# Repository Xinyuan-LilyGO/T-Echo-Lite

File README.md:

<!--
 * @Description: None
 * @Author: LILYGO_L
 * @Date: 2023-09-11 16:13:14
 * @LastEditTime: 2026-07-14 09:57:59
 * @License: GPL 3.0
-->
<h1 align = "center">T-Echo-Lite</h1>

## **English | [中文](./README_CN.md)**

## Version iteration:
| Version                              | Update date                       |
| :-------------------------------: | :-------------------------------: |
| T-Echo-Lite_V1.0            | 2024-12-06                         |
| T-Echo-Lite-Kit_V1.0            | 2025-10-14                         |

## PurchaseLink
| Product                     | SOC           |  FLASH  |  PSRAM   | Link                   |
| :------------------------: | :-----------: |:-------: | :---------: | :------------------: |
| T-Echo-Lite_V1.0   | nRF52840 |   1M   |256kB| [LILYGO Mall](https://lilygo.cc/products/t-echo-lite?_pos=1&_sid=79b4c08e7&_ss=r&variant=45331277906101) |
| T-Echo-Lite-Kit_V1.0   |  |  || NULL |

## Directory
- [Describe](#describe)
- [Preview](#preview)
- [Module](#module)
- [SoftwareDeployment](#SoftwareDeployment)
- [PinOverview](#pinoverview)
- [RelatedTests](#RelatedTests)
- [FAQ](#faq)
- [Project](#project)

## Describe

T-Echo-Lite is a lightweight version based on T-Echo, featuring a smaller volume and lower power consumption design compared to T-Echo. Its minimum deep sleep power consumption can reach 2μA to 10μA (due to differences in onboard components on different boards, power consumption performance may vary; the minimum power consumption mentioned here is based on the engineering board tested by the LILYGO laboratory). The board is equipped with a rich set of features, including an inertial sensor, LORA module, solar charging function (5V), external GPS, and more. Its excellent power consumption performance allows T-Echo-Lite to achieve superior battery life.

T-Echo-Lite-Kit is a baseboard expansion for T-Echo-Lite, primarily extending peripherals such as a keyboard, speaker, microphone, and vibration motor.

> [!NOTE]
> T-Echo-Lite-Kit and T-Echo-Lite-KeyShield refer to the same product. The legacy name is retained only in existing file and directory names.

> [!IMPORTANT]
> Important note: The L76K module and the ICM20948 module are external expansion modules. The default purchase link does not include these two modules (the ICM20948 module is connected via soldering, while the L76K module is connected via pin headers). They need to be purchased separately.

## Preview

### Actual Product Image

---

---

## Module

### T-Echo-Lite Section
### 1. MCU
*   Chip: nRF52840
*   RAM: 256kB
*   FLASH: 1M
*   Related Documentation:
    > [nRF52840_Datasheet](https://docs.nordicsemi.com/bundle/ps_nrf52840/page/keyfeatures_html5.html)

### 2. Screen
*   Name: GDEM0122T61
*   Size: 1.22 inches
*   Resolution: 176x192px
*   Screen Type: E-PAPER
*   Driver Chip: SSD1681
*   Bus Communication Protocol: IIC
*   Additional Notes: Fast refresh is not supported (after consulting the screen manufacturer, they replied that it is not supported), it is recommended to use full refresh only
*   Dependent Libraries:
    >[Adafruit_EPD](https://github.com/adafruit/Adafruit_EPD)  
    >[Adafruit_BusIO](https://github.com/adafruit/Adafruit_BusIO)  
    >[Adafruit_SPIFlash](https://github.com/adafruit/Adafruit_SPIFlash)  
    >[Adafruit-GFX-Library](https://github.com/adafruit/Adafruit-GFX-Library)
*   Related Documentation:
    > [GDEM0122T61](./information/GDEM0122T61.pdf)  
    > [SSD1681](./information/SSD1681.pdf)  

### 3. LORA
*   Chip Module: S62F
*   Chip: SX1262
*   Bus Communication Protocol: SPI
*   Dependent Libraries:
    >[RadioLib](https://github.com/jgromes/RadioLib)  
    >[Adafruit_BusIO](https://github.com/adafruit/Adafruit_BusIO)  
    >[Adafruit_SPIFlash](https://github.com/adafruit/Adafruit_SPIFlash)
*   Related Documentation:
    > [S62F](./information/S62F.pdf)  
    > [S62F Application Note](./information/S62F_ApplicationNote_Ver_D.pdf)

#### S62F Hardware Configuration

* RF switch: T-Echo-Lite uses AcSiP control mode A. The nRF52840 drives `RF_VC1` (`P0.27`) and `RF_VC2` (`P1.01`) directly. `DIO2` (`P0.05`) is routed separately and is not hardwired to the RF switch on this board. Set `RF_VC1/RF_VC2` to `HIGH/LOW` for transmit and `LOW/HIGH` for receive.
* TCXO: The embedded 32 MHz TCXO is controlled internally by SX1262 `DIO3`. Set `tcxoVoltage` explicitly to `3.0 V` when initializing the radio.
* Regulator: `VREG` and `DCC_SW` are connected through a 15 uH inductor. Use the DC-DC regulator mode (`useRegulatorLDO = false`).

### 4. GPS
*   Chip Module: L76K
*   Bus Communication Protocol: UART
*   Dependent Libraries:
    >[TinyGPSPlus](https://github.com/mikalhart/TinyGPSPlus)
*   Related Documentation:
    > [L76KB-A58](./information/L76KB-A58.pdf)  

> [!IMPORTANT]
> Important note: The L76K module is an external expansion module. The default purchase link does not include this module, so it needs to be purchased separately.

### 5. Inertial Measurement Unit
*   Chip: ICM20948
*   Bus Communication Protocol: IIC
*   Dependent Libraries:
    >[ICM20948_WE](https://github.com/wollewald/ICM20948_WE)
*   Related Documentation:
    > [ICM20948](./information/ICM20948.pdf)  

> [!IMPORTANT]
> Important note: The ICM20948 module is an external expansion module. The default purchase link does not include this module, so it needs to be purchased separately.

### 6. Flash
*   Chip: ZD25WQ32C or ZD25Q32D
*   Bus Communication Protocol: SPI
*   Dependent Libraries:
    >[Adafruit_BusIO](https://github.com/adafruit/Adafruit_BusIO)  
    >[Adafruit_SPIFlash](https://github.com/adafruit/Adafruit_SPIFlash)  
*   Related Documentation:
    > [ZD25WQ32CEIGR](./information/ZD25WQ32CEIGR.pdf)
    >[ZD25Q32DTIGT](./information/ZD25Q32DTIGT.pdf)

### T-Echo-Lite-Kit Section
### 1. Keyboard Backlight

* Driver Chip: AW21009QNR
* Bus Communication Protocol: IIC
* Dependent Libraries:
    >[cpp_bus_driver](https://github.com/Llgok/cpp_bus_driver)
* Related Information:
    >[AW21009QNR](./information/AW21009QNR.pdf)

### 2. Vibration

* Driver Chip: AW86224
* Bus Communication Protocol: IIC
* Dependent Libraries:
    >[cpp_bus_driver](https://github.com/Llgok/cpp_bus_driver)
* Related Information:
    >[AW86224AFCR](./information/AW86224AFCR.pdf)

### 3. Speaker Microphone

* Driver Chip: ES8311
* Bus Communication Protocols: IIC, IIS
* Dependent Libraries:
    >[cpp_bus_driver](https://github.com/Llgok/cpp_bus_driver)
* Related Information:
    >[ES8311](./information/ES8311.pdf)

### 4. Keyboard

* Driver Chip: TCA8418
* Bus Communication Protocol: IIC
* Dependent Libraries:
    >[cpp_bus_driver](https://github.com/Llgok/cpp_bus_driver)
* Related Information:
    >[tca8418](./information/tca8418.pdf)

## SoftwareDeployment

### Examples Support

### T-Echo-Lite Examples
| Example | `[Arduino IDE (Adafruit_nRF52_V1.6.1)]` <br /> `[PlatformIO (nordicnrf52_V10.6.0)]` <br /> Support | Description | Picture |
| ------  | ------  | ------ | ------ | 
| [Battery_Measurement](./examples/T-Echo-Lite/Battery_Measurement) | <p align="center">![alt text][supported]  |  |  |
| [BLE_Uart](./examples/T-Echo-Lite/BLE_Uart) | <p align="center">![alt text][supported]  |  |  |
| [Button_Triggered](./examples/T-Echo-Lite/Button_Triggered) | <p align="center">![alt text][supported]  |  |  |
| [Display](./examples/T-Echo-Lite/Display) | <p align="center">![alt text][supported]  |  |  |
| [Display_BLE_Uart](./examples/T-Echo-Lite/Display_BLE_Uart) | <p align="center">![alt text][supported]  |  |  |
| [Display_SX1262](./examples/T-Echo-Lite/Display_SX1262) | <p align="center">![alt text][supported]  |  |  |
| [Flash](./examples/T-Echo-Lite/Flash) | <p align="center">![alt text][supported]  |  |  |
| [Flash_Erase](./examples/T-Echo-Lite/Flash_Erase) | <p align="center">![alt text][supported]  |  |  |
| [Flash_Speed_Test](./examples/T-Echo-Lite/Flash_Speed_Test) | <p align="center">![alt text][supported]  |  |  |
| [GPS](./examples/T-Echo-Lite/GPS) | <p align="center">![alt text][supported]  |  |  |
| [GPS_Full](./examples/T-Echo-Lite/GPS_Full) | <p align="center">![alt text][supported]  |  |  |
| [ICM20948](./examples/T-Echo-Lite/ICM20948) | <p align="center">![alt text][supported]  |  |  |
| [IIC_Scan_2](./examples/T-Echo-Lite/IIC_Scan_2) | <p align="center">![alt text][supported]  |  |  |
| [nrf52840_module](./examples/T-Echo-Lite/nrf52840_module) | <p align="center">![alt text][supported]  |  |  |
| [Original_Test](./examples/T-Echo-Lite/Original_Test) |<p align="center">![alt text][supported]  | Product factory original testing |  |
| [Sleep_Wake_Up](./examples/T-Echo-Lite/Sleep_Wake_Up) | <p align="center">![alt text][supported]  |  |  |
| [SX126x_PingPong](./examples/T-Echo-Lite/SX126x_PingPong) | <p align="center">![alt text][supported]  |  |  |
| [SX126x_PingPong_2](./examples/T-Echo-Lite/SX126x_PingPong_2) | <p align="center">![alt text][supported]  |  |  |
| [sx126x_tx_continuous_wave](./examples/T-Echo-Lite/sx126x_tx_continuous_wave) | <p align="center">![alt text][supported]  |  |  |

### T-Echo-Lite-Kit Examples
| Example | `[Arduino IDE (Adafruit_nRF52_V1.6.1)]` <br /> `[PlatformIO (nordicnrf52_V10.6.0)]` <br /> Support | Description | Picture |
| ------  | ------  | ------ | ------ | 
| [aw21009qnr](./examples/T-Echo-Lite-KeyShield/aw21009qnr) | <p align="center">![alt text][supported]  |  |  |
| [aw86224](./examples/T-Echo-Lite-KeyShield/aw86224) | <p align="center">![alt text][supported]  |  |  |
| [es8311](./examples/T-Echo-Lite-KeyShield/es8311) | <p align="center">![alt text][supported]  |  |  |
| [general_test](./examples/T-Echo-Lite-KeyShield/general_test) | <p align="center">![alt text][supported]  | Product factory original testing  |  |
| [tca8418](./examples/T-Echo-Lite-KeyShield/tca8418) | <p align="center">![alt text][supported]  |  |  |
| [voice_speaker](./examples/T-Echo-Lite-KeyShield/voice_speaker) | <p align="center">![alt text][supported]  |  |  |

[supported]: https://img.shields.io/badge/-supported-green "example"

| Bootloader | Description | Picture |
| ------  | ------  | ------ |
| [bootloader](./bootloader/) | |  |

| Firmware | Description | Picture |
| ------  | ------  | ------ |
| [T-Echo-Lite_Original_Test](./firmware/[T-Echo-Lite_V1.0][Original_Test]_firmware/)| Product factory original testing |  |
| [T-Echo-Lite-Kit_general_test](./firmware/[T-Echo-Lite-KeyShield_V1.0][general_test]_firmware/)| Product factory original testing |  |

### IDE and Flashing

#### PlatformIO
1. Install [VisualStudioCode](https://code.visualstudio.com/Download),choose installation based on your system type.

2. Open the "Extension" section of the Visual Studio Code software sidebar (Alternatively, use "<kbd>Ctrl</kbd>+<kbd>Shift</kbd>+<kbd>X</kbd>" to open the extension). Search for the "PlatformIO IDE" extension and download it.

3. During the installation of the extension, you can go to GitHub to download the program. You can download the main branch by clicking on the "<> Code" with green text, or you can download the program versions from the "Releases" section in the sidebar.

4. After the installation of the extension is completed, open the Explorer in the sidebar (Alternatively, use "<kbd>Ctrl</kbd>+<kbd>Shift</kbd>+<kbd>E</kbd>" go open it). Click on "Open Folder", locate the project code you just downloaded (the entire folder), and click "Add." At this point, the project files will be added to your workspace.

5. Open the "platformio.ini" file in the project folder (PlatformIO will automatically open the "platformio.ini" file corresponding to the added folder). Under the "[platformio]" section, uncomment and select the example program you want to burn (it should start with "default_envs = xxx") Then click "<kbd>[√](image/4.png)</kbd>" in the bottom left corner to compile. If the compilation is correct, connect the microcontroller to the computer and click "<kbd>[→](image/5.png)</kbd>" in the bottom left corner to download the program.

6. At this point, an error may occur, and you need to install [Python](https://www.python.org/downloads/). Open the folder "tool" -> "win10 vscode platformio start" sequentially, and execute the cmd command `python t-echo-lite_v1.0.0_setup.py` under the "win10 vscode platformio start" folder. This will complete the development board installation, and the compilation and flashing will no longer report errors.

#### Arduino

1. Install [Arduino](https://www.arduino.cc/en/software), and select the installation based on your system type.

2. Open the "example" directory of the project folder, select the example project folder, and open the file ending with ".ino" to open the Arduino IDE project workspace.

3. Open the "Tools" menu bar at the top right -> Select "Board" -> "Board Manager", find or search for "Adafruit_nRF52", and download the board file with the author named "Adafruit". Then return to the "Board" menu bar, select the board type under the "Adafruit_nRF52" board, and the selected board type is determined by the "board = xxx" header under the [env] directory in the "platformio.ini" file. If there is no corresponding board, you need to manually add the board under the "board" directory in the project folder. (If "Adafruit_nRF52" cannot be found, you need to open Preferences -> Add `https://www.adafruit.com/package_adafruit_index.json` to "Additional Board Manager URLs")
    
4. Open the menu bar "[File](image/6.png)" -> "[Preferences](image/6.png)", find the "[Project Folder Location](image/7.png)" section, and copy and paste all the library files along with the folders in the "libraries" folder under the project directory into the "libraries" folder in this directory.
    
5. Select the correct settings in the "Tools" menu, as shown in the table below.
    
| Setting                               | Value                                 |
| :-------------------------------: | :-------------------------------: |
| Board                                 | Nordic nRF52840 DK           |

6.  Select the correct port.

7.  Enable boot download mode: Press and release the RST chip reset button, wait for LED1 to light up (you must wait for LED1 to light up), then press and release the RST button again. Observe that LED1 gradually dims and then gradually lights up, indicating that the boot download mode has been entered.

8.  Click the top right "[√](image/8.png)" to compile. If there are no errors, connect the microcontroller to the computer and click the top right "[→](image/9.png)" to start the flashing process.

#### JLINK Flashing Firmware and Bootloader

1.  Install the software [nRF-Connect-for-Desktop](https://www.nordicsemi.com/Products/Development-tools/nRF-Connect-for-Desktop/Download#infotabs)

2.  Install the software [JLINK](https://www.segger.com/downloads/jlink/)

3.  Connect the JLINK pins correctly as shown in the figure below

4.  Open the software nRF-Connect-for-Desktop and install the tool [Programmer](./image/10.png) and open it

5.  Add files, select both the bootloader file and the firmware file at the same time, click [Erase&write](./image/11.png), and the flashing will be completed.

## PinOverview

For pin definitions, please refer to the configuration file: 
<br />

[t_echo_lite_config.h](./libraries/private_library/t_echo_lite_config.h)  
[t_echo_lite_keyshield_config.h](./libraries/private_library/t_echo_lite_keyshield_config.h)

## RelatedTests

### Power Dissipation
| Firmware | Program| Description | Picture |
| ------  | ------  | ------ | ------ | 
| [Sleep_Wake_Up](./firmware/[T-Echo-Lite_V1.0][Sleep_Wake_Up]_firmware/[T-Echo-Lite_V1.0][Sleep_Wake_Up]_firmware_202412040900.hex) <br /> [Sleep_Wake_Up(uf2)](./firmware/[T-Echo-Lite_V1.0][Sleep_Wake_Up]_firmware/[T-Echo-Lite_V1.0][Sleep_Wake_Up]_firmware_202412040900.uf2) | `Sleep_Wake_Up` | Minimum power consumption: 2.54uA <br /> More information can be found in the [Power Consumption Test Log](./relevant_test/PowerConsumptionTestLog_[T-Echo-Lite_V1.0]_20241210.pdf) |  |

## FAQ

* Q. After reading the above tutorials, I still don't know how to build a programming environment. What should I do?
* A. If you still don't understand how to build an environment after reading the above tutorials, you can refer to the [LilyGo-Document](https://github.com/Xinyuan-LilyGO/LilyGo-Document) document instructions to build it.

<br />

* Q. Why does Arduino IDE prompt me to update library files when I open it? Should I update them or not?
* A. Choose not to update library files. Different versions of library files may not be mutually compatible, so it is not recommended to update library files.

<br />

* Q. Why is there no debug information output from my board's USB?
* A. Please enable the "DTR" option in your serial assistant software.

<br />

* Q. Why does my board fail to flash when I use USB directly?
* A. Please press and release the RST chip reset button, wait for LED1 to light up (you must wait for LED1 to light up), then press and release the RST button again. Observe that LED1 gradually dims and then gradually lights up, indicating that the boot download mode has been entered. At this point, you can flash the board.

<br />

* Q. How should the Bluetooth antenna and Lora antenna of the T-Echo-Lite module be distinguished?
* A. The Bluetooth antenna and Lora antenna of the T-Echo-Lite module are as shown in the following figure:

<br />

## Project
* [T-Echo-Lite_V1.0](./project/T-Echo-Lite_V1.0)
* [T-Echo-Lite-Kit_V1.0](./project/T-Echo-Lite-KeyShield_V1.0)

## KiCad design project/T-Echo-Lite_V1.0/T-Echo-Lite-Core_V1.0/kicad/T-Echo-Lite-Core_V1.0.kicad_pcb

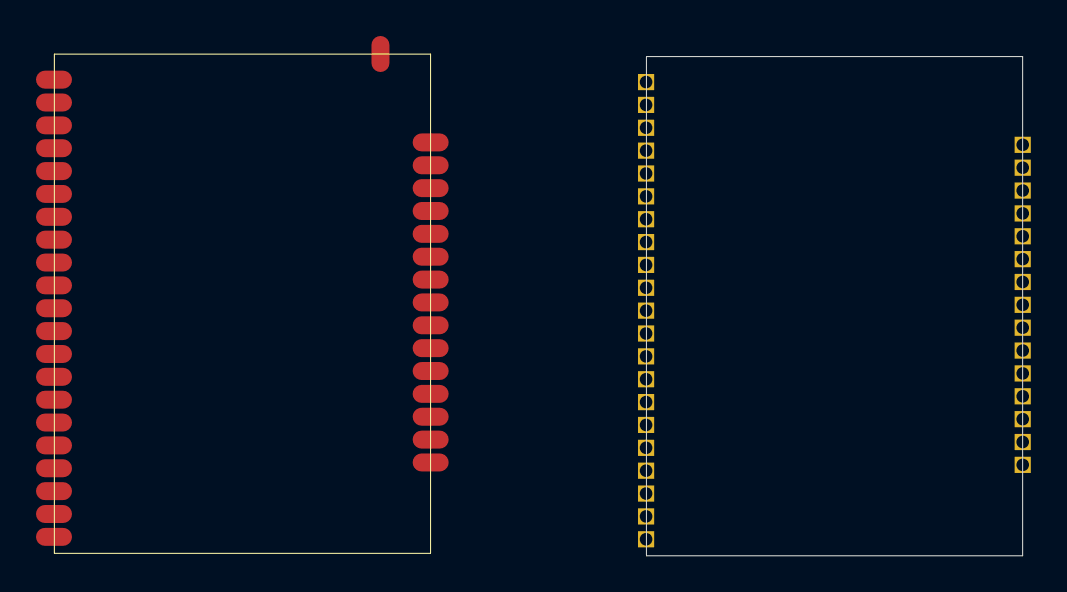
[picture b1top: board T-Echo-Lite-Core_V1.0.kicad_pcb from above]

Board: 2 copper layers, 20.9 x 27.7 mm, 3 parts (0 on the bottom side), 26 nets, no tracks yet.

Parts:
P0: SPAD___21
P3: SPAD___15
U?: T_Ech0_lite

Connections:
BUTTON: P0.9, U?.9
GND: P0.19, U?.19
P0.16: P3.13, U?.24
P0.23: P3.10, U?.27
P0.25: P3.9, U?.28
P0.29: P0.3, U?.3
P1.02: P3.8, U?.29
P1.03: P3.3, U?.34
P1.04: P3.7, U?.30
P1.05: P3.2, U?.35
P1.06: P3.6, U?.31
P1.07: P3.1, U?.36
P1.10: P0.4, U?.4
P1.11: P0.5, U?.5
P1.15: P0.2, U?.2
REST: P0.12, U?.12
SWDCLK: P0.11, U?.11
SWDIO: P0.10, U?.10
S_PWR: P0.21, U?.21
USB_D+: P0.14, U?.14
USB_D-: P0.13, U?.13
VBAT: P0.20, U?.20
VBUS: P0.18, U?.18
VDD3V3: P0.15, U?.15
VDDH: P0.17, U?.17
VDD_NRF: P0.16, U?.16

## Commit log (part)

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2024-11-27 Create Project
2024-12-10 Fix errors in PowerConsumptionTestLog
2024-12-14 Fix some errors in the document
2025-01-02 Update more examples
2025-01-02 Update issue template
2025-01-06 Fix some errors and update examples
2025-01-23 Fix Lora and GPS errors
2025-02-12 Fix the issue where the Original_Test program gets stuck during the Lora test.
2025-02-19 fix bugs
2025-02-24 Update Lora Example
2025-03-13 Add RT9080_ EN switch
2025-03-17 Fix shallow sleep awakening issues
2025-03-28 Update test item sx126x_tx_comtinuous-wave
2025-04-01 modify feature request template
2025-04-28 Add lora_certification test
2025-05-12 Update lora_certification
2025-05-22 Update T_Echo_lite.PcbLib #1
2025-05-24 Update README #2
2025-05-24 Update T_Echo_lite.SchLib #1
2025-06-04 Update nrf52840_module
2025-06-04 Update the description of the Bluetooth antenna and LoRa antenna.
2025-06-05 update T-Echo-Lite-Core_V1.0 #1
2025-06-05 Modify the Chinese comments in the example to English. #5
2025-06-05 Update Adafruit_nRF52_Bootloader_t-echo_lite_nrf52840
2025-06-09 Update structure #1
2025-06-10 Update the top-level and bottom-layer 3D diagrams of T-Echo-lite. #2
2025-06-10 Update Adafruit_nRF52_Bootloader
2025-06-10 Change bootloader name
2025-07-15 Update Original_Test
2025-07-15 Update variant
2025-08-19 update T-Echo-Lite-KeyShield
2025-08-20 update tca8418
2025-08-22 update sx126x_tx_continuous_wave
2025-08-29 add es8311 example
2025-08-29 update es8311 example
2025-09-01 fix the popping sound issue after iis transmission is completed
2025-09-01 add aw86224 example
2025-09-02 update microphone speaker example
2025-09-03 update cpp_bus_driver
2025-09-12 update firmware
2025-09-12 updata t_echo_lite_keyshield_config
2025-09-25 update T-Echo-Lite-KeyShield example
2025-10-16 update T-Echo-Lite-KeyShield README
2025-10-16 update private_library
2025-10-30 add lora interruption clear flag
2025-11-14 add partial screen refresh functionality and fix screen refresh stuttering issues
2025-11-14 update T-Echo-Lite-KeyShield original_test
2025-12-10 fix the issue of speaker playback noise
2025-12-17 update [nRF52840_Module_V1.0][nrf52840_module(lora_433mhz)]_firmware_202512171348
2026-01-21 update [T-Echo-Lite_V1.0][Original_Test(lora_920mhz_125khz)]_firmware
2026-02-27 update meshtastic
2026-03-02 update MeshCore
2026-04-09 update the original_test example of T-Echo-Lite-KeyShield to automatically enter light sleep functionality
2026-04-14 update the iis of the CPP_BUS_DRIVER_DEVELOPMENT_FRAMEWORK_ARDUINO_NRF framework to adapt it to the latest cpp_bus_driver library
2026-04-23 Fix the bug in the set_brightness function of aw21009xxx
2026-04-25 Update ws2812
2026-05-16 Add purchase default configuration notes for L76K module and ICM20948 module #11
2026-05-16 fix: V-003 security vulnerability
    Automated security fix generated by Orbis Security AI
2026-06-03 Updated to adapt to cpp_bus_driver v2.2.0.
2026-06-03 Change the name of original_test to general_test.
2026-06-03 Updated general_test to integrate with LVGL.
2026-06-04 Updated general_test
2026-06-04 Updated general_test mic and speaker
2026-06-04 Organize the file view and modify the global refresh method to prioritize partial refresh.
2026-06-05 Fix screen refresh issue.
2026-06-05 Add function comments to battery_view.
2026-06-08 Updated firmware
2026-06-10 Add volatile to prevent the screen refresh variable from being optimized away by the compiler.
